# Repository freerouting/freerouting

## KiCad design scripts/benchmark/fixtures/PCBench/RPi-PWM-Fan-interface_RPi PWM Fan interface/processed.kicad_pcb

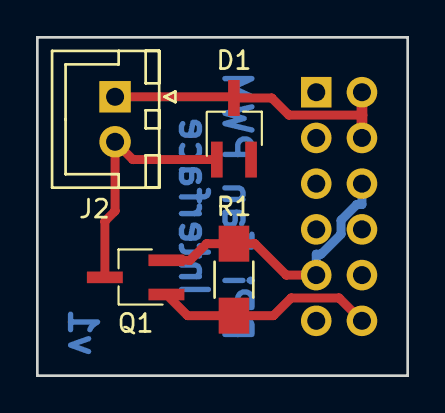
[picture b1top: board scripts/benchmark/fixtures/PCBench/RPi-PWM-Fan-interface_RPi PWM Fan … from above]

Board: 2 copper layers, 20.6 x 18.8 mm, 5 parts (0 on the bottom side), 4 nets.

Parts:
D1: Schottky; TSOT-23_HandSoldering
J1: CONN_02X06; Socket_Strip_Straight_2x06_Pitch2.54mm
J2: JST_XH_01X02; JST_XH_B02B-XH-A_02x2.50mm_Straight
Q1: MOSFET; TSOT-23_HandSoldering
R1: 100K; R_1206_HandSoldering

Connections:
+5V: D1.3, J1.2, J1.4, J2.1
GND: J1.6, J1.9, Q1.2, R1.2
unnamed: D1.1, J2.2, Q1.3
unnamed: J1.12, Q1.1, R1.1

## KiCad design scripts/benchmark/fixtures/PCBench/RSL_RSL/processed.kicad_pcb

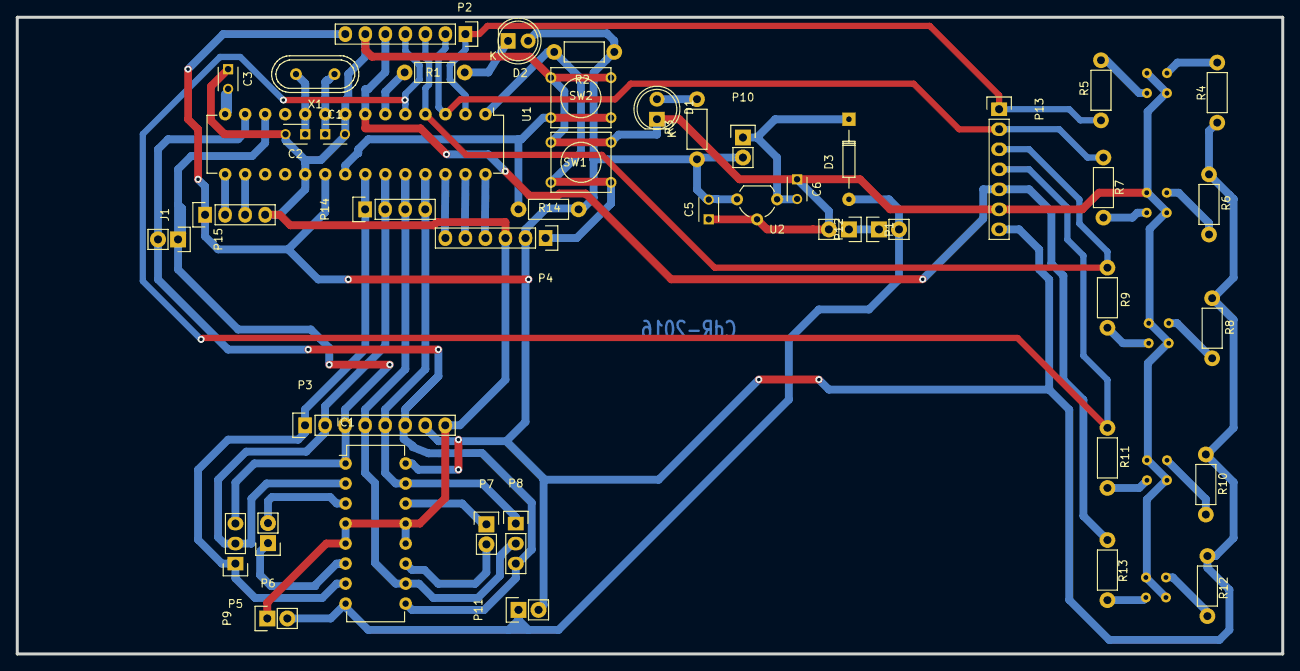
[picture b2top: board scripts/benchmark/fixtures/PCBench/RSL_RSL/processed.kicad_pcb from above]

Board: 2 copper layers, 160.5 x 80.8 mm, 49 parts (0 on the bottom side), 43 nets.

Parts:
C1: C-crsital; C_Disc_D3_P2.5
C2: C-cristal; C_Disc_D3_P2.5
C3: C; C_Disc_D3_P2.5
C5, C6: C-reg; C_Disc_D3_P2.5
D1: PWR; LED-5MM
D2: RUN; LED-5MM
D3: D_Small; Diode_DO-35_SOD27_Horizontal_RM10
IC1: L293D; DIP-16_W7.62mm
J1: USB; Pin_Header_Straight_1x04
P1: Alimentacion; Pin_Header_Straight_1x02
P2, P13: Pines_Sensores; Socket_Strip_Straight_1x07
P3: Pines_ Driver_M; Socket_Strip_Straight_1x08
P4: pickit; Socket_Strip_Straight_1x06
P5: 2A-1A-1.2E; Pin_Header_Straight_1x03
P6: motor1; Pin_Header_Straight_1x02
P7: motor2; Pin_Header_Straight_1x02
P8: E3.4-3A-4A; Pin_Header_Straight_1x03
P9: alimtacionMOTORES; Pin_Header_Straight_1x02
P10: BAT; Pin_Header_Straight_1x02
P11: jp1; Pin_Header_Straight_1x02
P12: PWRSW; Pin_Header_Straight_1x02
P14: Ctrl_Dir; Pin_Header_Straight_1x04
P15: PWM; Pin_Header_Straight_1x02
R1: 470; Resistor_Horizontal_RM7mm
R2: 10K; Resistor_Horizontal_RM7mm
R3, R4, R5, R6, R7, R8, R9, R10, R11, R12, R13, R14: R; Resistor_Horizontal_RM7mm
SW1: reset; SW_PUSH_SMALL
SW2: int0; SW_PUSH_SMALL
U1: PIC18F2550; DIP-28_W7.62mm
U2: 7805; TO-92_Molded_Wide
U3, U4, U5, U6, U7: CNY70; cny70-4
X1: CRYSTAL; Crystal_HC49-U_Vertical

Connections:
/0: R14.2, SW2.1, U1.21
/5: P4.6, U1.26
/6: P4.5, U1.27
/7: P4.4, U1.28
/D+: J1.3, U1.16
/D-: J1.2, U1.15
/driver_motores/1A: IC1.2, P3.2, P5.2, P14.2, U1.23
/driver_motores/2A: IC1.7, P3.1, P5.1, P14.1, U1.22
/driver_motores/3A: IC1.10, P3.4, P8.2, P14.3, U1.24
/driver_motores/4A: IC1.15, P3.5, P8.1, P14.4, U1.25
/driver_motores/E-1.2: IC1.1, P3.3, P5.3, P15.1, U1.12
/driver_motores/E-3.4: IC1.9, P3.6, P8.3, P15.2, U1.13
/r: P4.1, R2.2, SW1.2, U1.1
/run: R1.2, U1.6
/sensores/sens0: P2.1, P13.1, R5.1, U1.2
/sensores/sens1: P2.2, P13.2, R7.1, U1.3
/sensores/sens2: P2.3, P13.3, R9.1, U1.4
/sensores/sens3: P2.4, P13.4, R11.1, U1.5
/sensores/sens4: P2.5, P13.5, R13.1, U1.7
GND: C1.2, C2.2, C3.1, C5.1, C6.1, D1.1, IC1.4, IC1.5, IC1.12, IC1.13, J1.4, P1.2, P2.6, P3.8, P4.3, P9.1, P13.6, SW1.1, SW2.2, U1.8, U1.19, U2.2, U3.E, U3.K, U4.E, U4.K, U5.E, U5.K, U6.E, U6.K, U7.E, U7.K
unnamed: C1.1, U1.9, X1.1
unnamed: C2.1, U1.10, X1.2
unnamed: C3.2, U1.14
unnamed: C6.2, D3.1, P10.1, U2.1
unnamed: D1.2, R3.2
unnamed: D2.1, R1.1
unnamed: IC1.3, P6.2
unnamed: IC1.6, P6.1
unnamed: IC1.11, P7.2
unnamed: IC1.14, P7.1
unnamed: P1.1, P12.1
unnamed: R4.2, U3.A
unnamed: R5.2, U3.C
unnamed: R6.2, U4.A
unnamed: R7.2, U4.C
unnamed: R8.2, U5.A
unnamed: R9.2, U5.C
unnamed: R10.2, U6.A
unnamed: R11.2, U6.C
unnamed: R12.2, U7.A
unnamed: R13.2, U7.C
VCC: C5.2, D2.2, IC1.16, J1.1, P2.7, P3.7, P4.2, P10.2, P11.2, P13.7, R2.1, R3.1, R4.1, R6.1, R8.1, R10.1, R12.1, R14.1, U1.20, U2.3
VCC2: D3.2, IC1.8, P9.2, P11.1, P12.2

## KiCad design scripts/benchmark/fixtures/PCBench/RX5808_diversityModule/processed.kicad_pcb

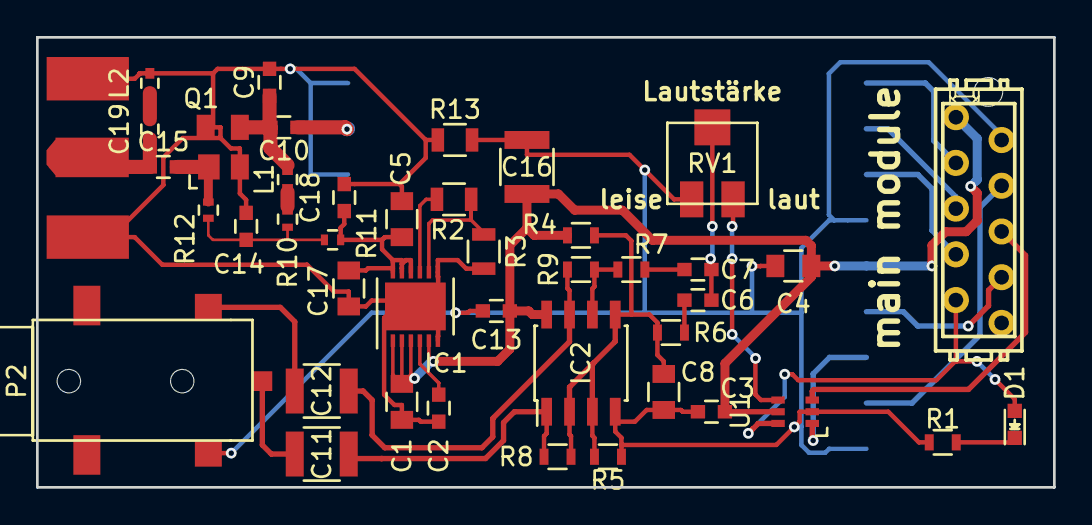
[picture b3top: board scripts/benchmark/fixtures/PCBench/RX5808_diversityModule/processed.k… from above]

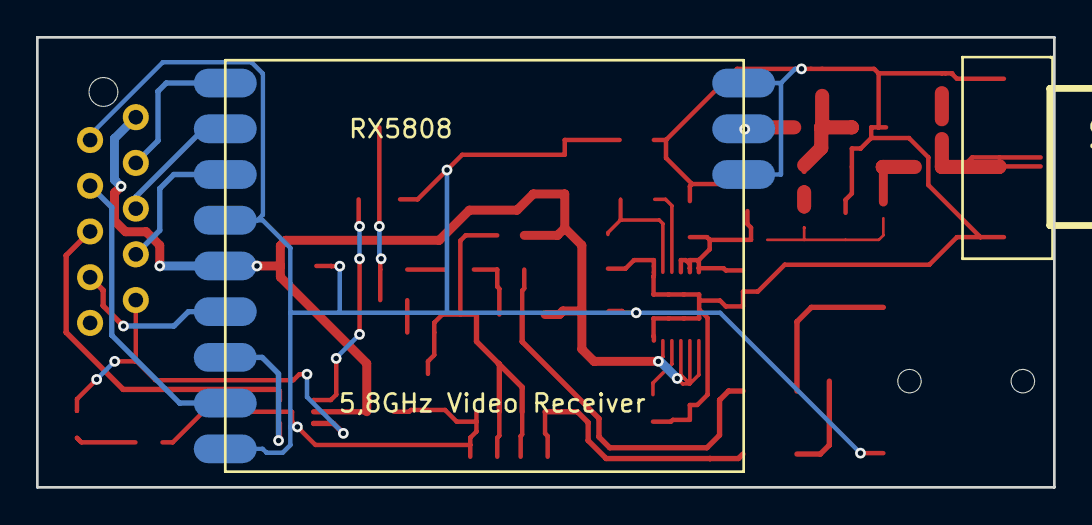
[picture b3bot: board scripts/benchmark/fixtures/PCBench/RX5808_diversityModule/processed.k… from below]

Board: 2 copper layers, 56.5 x 25.0 mm, 44 parts (2 on the bottom side), 33 nets.

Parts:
C1, C4, C5, C17: 10u; C_0805
C2: 10n; C_0603
C3, C13, C18: 100n; C_0603
C6, C7: 1u; C_0603
C8: 22u; C_0805
C9, C10: 1p; C_0603
C11, C12, C16: 100µ; C_1210
C14: 33pF; C_0603
C15: 22p; C_0603
C19: 2,2pF; C_0402
D1: red; LED_0603
IC1: LP38798; DFN-12-1EP_4x4mm_Pitch0.5mm
IC2: TDA1308A; SOIC-8_3.9x4.9mm_Pitch1.27mm
L1: 1,8nH; R_0402
L2: 1,8nH; C_0402
P1: CONN_02X05; MICROMATCH-10
P2: CONN_01X03; LUM1503-03
Q1: BFP840; SOT-143
R1: 220; R_0603
R2: 21k 0,1%; R_0805
R3: 14k 0,1%; R_0805
R4, R5: 10k; R_0603
R6, R7: 3,9k; R_0603
R8, R9: 39k; R_0603
R10, R11: 51; R_0402
R12: 27k; R_0402
R13: 0; R_0805
RV1: POT; Poti-SMD-Model-23A
SMA_E1: SMA_EDGE; SMA_EDGE_Johnson_142-0701-801
U1: sn74lvc1g3157; SC-70-6
U2: RX5808

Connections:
+5V: C1.1, C3.1, C4.1, C13.1, C16.1, IC1.1, IC1.2, IC1.3, IC1.5, IC2.8, P1.1, R4.1, U1.5, U2.8
/+3,0V: C5.1, C17.1, C18.1, IC1.10, IC1.11, IC1.12, R11.2
/audio1: P1.6, U1.3
/clk: P1.7, U2.6
/data: P1.3, U2.4
/rssi: P1.8, U2.9
/ss: P1.5, U2.5
/switch: D1.2, P1.9, U1.6
/video2: P1.4, U2.11
GND: C3.2, C4.2, C8.2, C13.2, C16.2, IC2.4, P1.2, P2.1, R1.2, R5.2, R13.1, RV1.3, U1.2, U2.7, U2.12
GNDA: C1.2, C2.2, C5.2, C9.2, C14.1, C17.2, C18.2, IC1.6, IC1.7, IC1.13, L2.2, Q1.2, Q1.4, R3.2, R13.2, SMA_E1.0, SMA_E1.2, U2.1, U2.3
unnamed: C2.1, IC1.4
unnamed: C6.1, R6.2
unnamed: C6.2, C7.2, RV1.2
unnamed: C7.1, R7.2
unnamed: C8.1, IC2.2, IC2.3, IC2.5, R4.2, R5.1, R6.1, R8.2
unnamed: C9.1, C10.1, L1.2, Q1.3
unnamed: C10.2, U2.2
unnamed: C11.1, IC2.1, R8.1
unnamed: C11.2, P2.2
unnamed: C12.1, IC2.7, R9.1
unnamed: C12.2, P2.3
unnamed: C14.2, R10.1, R11.1, R12.2
unnamed: C15.1, C19.1, SMA_E1.1
unnamed: C15.2, Q1.1, R12.1
unnamed: C19.2, L2.1
unnamed: D1.1, R1.1
unnamed: IC1.8, R2.2, R3.1
unnamed: IC1.9, R2.1
unnamed: IC2.6, R7.1, R9.2
unnamed: L1.1, R10.2
unnamed: RV1.1, U1.4
unnamed: U1.1, U2.10
